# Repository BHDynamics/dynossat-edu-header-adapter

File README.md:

# DynOSSAT-EDU-Header_Adapter
DynOSSAT-EDU is the first open source PocketQube educational kit compatible with CircuitPython and Arduino.

This plaform is equipped with all the necessary modules for the operation of a nanosatellite (PocketQube)
in Low Earth Orbit (LEO) that would serve as a device for teaching, training, and driving curiosity about the philosophy and technology related to NewSpace.

This repository contains the hardware files for the Header Adapter. It is a simple board to break out the 1.27mm 2x20 pin PQBH40 bus to two 2x10 pin 2.54 mm
headers so it's easier to use with standard Dupont cables. It also includes a LED connected to D3.

Hardware in this repository is licenced under **CERN OHL v1.2**.

## Documentation

Available soon!

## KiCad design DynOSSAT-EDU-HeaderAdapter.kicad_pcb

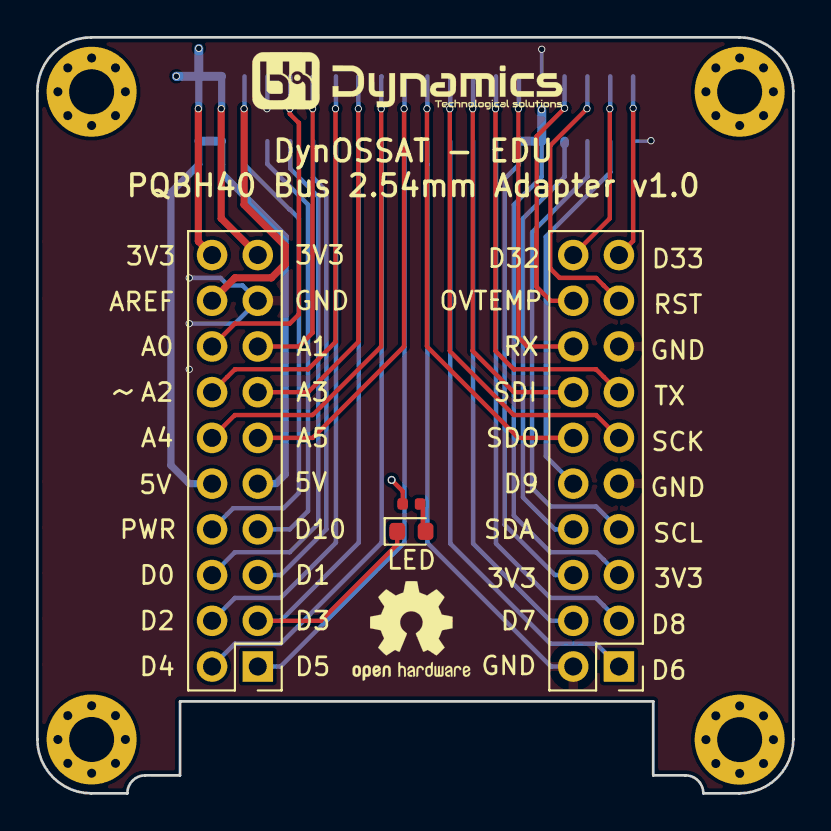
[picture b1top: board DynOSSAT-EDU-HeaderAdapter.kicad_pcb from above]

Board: 4 copper layers, 42.0 x 42.0 mm, 9 parts (1 on the bottom side), 34 nets.

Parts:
D1: LED; LED_0603_1608Metric
H1, H2, H3, H4: MountingHole_Pad; MountingHole_2.5mm_Pad_Via
J1: Conn_02x20_Odd_Even; PinSocket_2x20_P1.27mm_Vertical_SMD
J2, J3: Conn_02x10_Odd_Even; PinHeader_2x10_P2.54mm_Vertical
R1: 510R; R_0402_1005Metric

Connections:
/3V3: J1.2, J1.4, J1.29, J1.31, J2.19, J2.20, J3.5, J3.6, R1.1
/5V: J1.1, J1.3, J2.9, J2.10
/A0: J1.10, J2.16
/A1: J1.12, J2.15
/A2: J1.14, J2.14
/A3: J1.16, J2.13
/A4: J1.18, J2.12
/A5: J1.20, J2.11
/AREF: J1.6, J2.18
/D0: J1.9, J2.6
/D1: J1.11, J2.5
/D2: J1.13, J2.4
/D3: D1.1, J1.15, J2.3
/D4: J1.17, J2.2
/D5: J1.19, J2.1
/D6: J1.23, J3.1
/D7: J1.25, J3.4
/D8: J1.27, J3.3
/D9: J1.37, J3.10
/D10: J1.7, J2.7
/D13: J1.5, J2.8
/D30_TX: J1.28, J3.13
/D31_RX: J1.30, J3.16
/D32: J1.38, J3.20
/D33: J1.40, J3.19
/I2C_SCL: J1.35, J3.7
/I2C_SDA: J1.33, J3.8
/OVTEMP: J1.34, J3.18
/RST: J1.36, J3.17
/SPI_SCK: J1.24, J3.11
/SPI_SDI: J1.26, J3.14
/SPI_SDO: J1.22, J3.12
GND: J1.8, J1.21, J1.32, J1.39, J2.17, J3.2, J3.9, J3.15
unnamed: D1.2, R1.2

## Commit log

2020-10-15 First commit v1.0 RC
2020-10-16 Add README and LICENCE
2020-10-16 Unignore Output folder
2020-11-06 Change MISO/MOSI to SDI/SDO
